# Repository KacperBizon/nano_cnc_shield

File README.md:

# Arduino Nano CNC shield

### How to use
- Install [LaserGRBL](https://github.com/arkypita/LaserGRBL/releases)
- Upload [GRBL](https://github.com/gnea/grbl) code to Arduino 

### Components
* Arduino Nano
* 2x A4988 Stepper motor drivers
* 1x IRFZ44N N-CHANNEL MOSFET
* 1x LM7805 Voltage regulator with Heatsink (note the regulator is now rotated on the PCB)
* 1x 47, 1x 1k and 1x 10k resistor
* 3mm diode
* slide switch (SS12D00)
* 1x 1000uF 16V capacitor or 2x 100uF capacitors
* 1x 2.5mm JST XH-Style 2pin male connector
* male and female header pins

### Acknowledgments
The project is based on [DIY-Mini-CNC-Laser-Engraver](https://www.instructables.com/DIY-Mini-CNC-Laser-Engraver/)

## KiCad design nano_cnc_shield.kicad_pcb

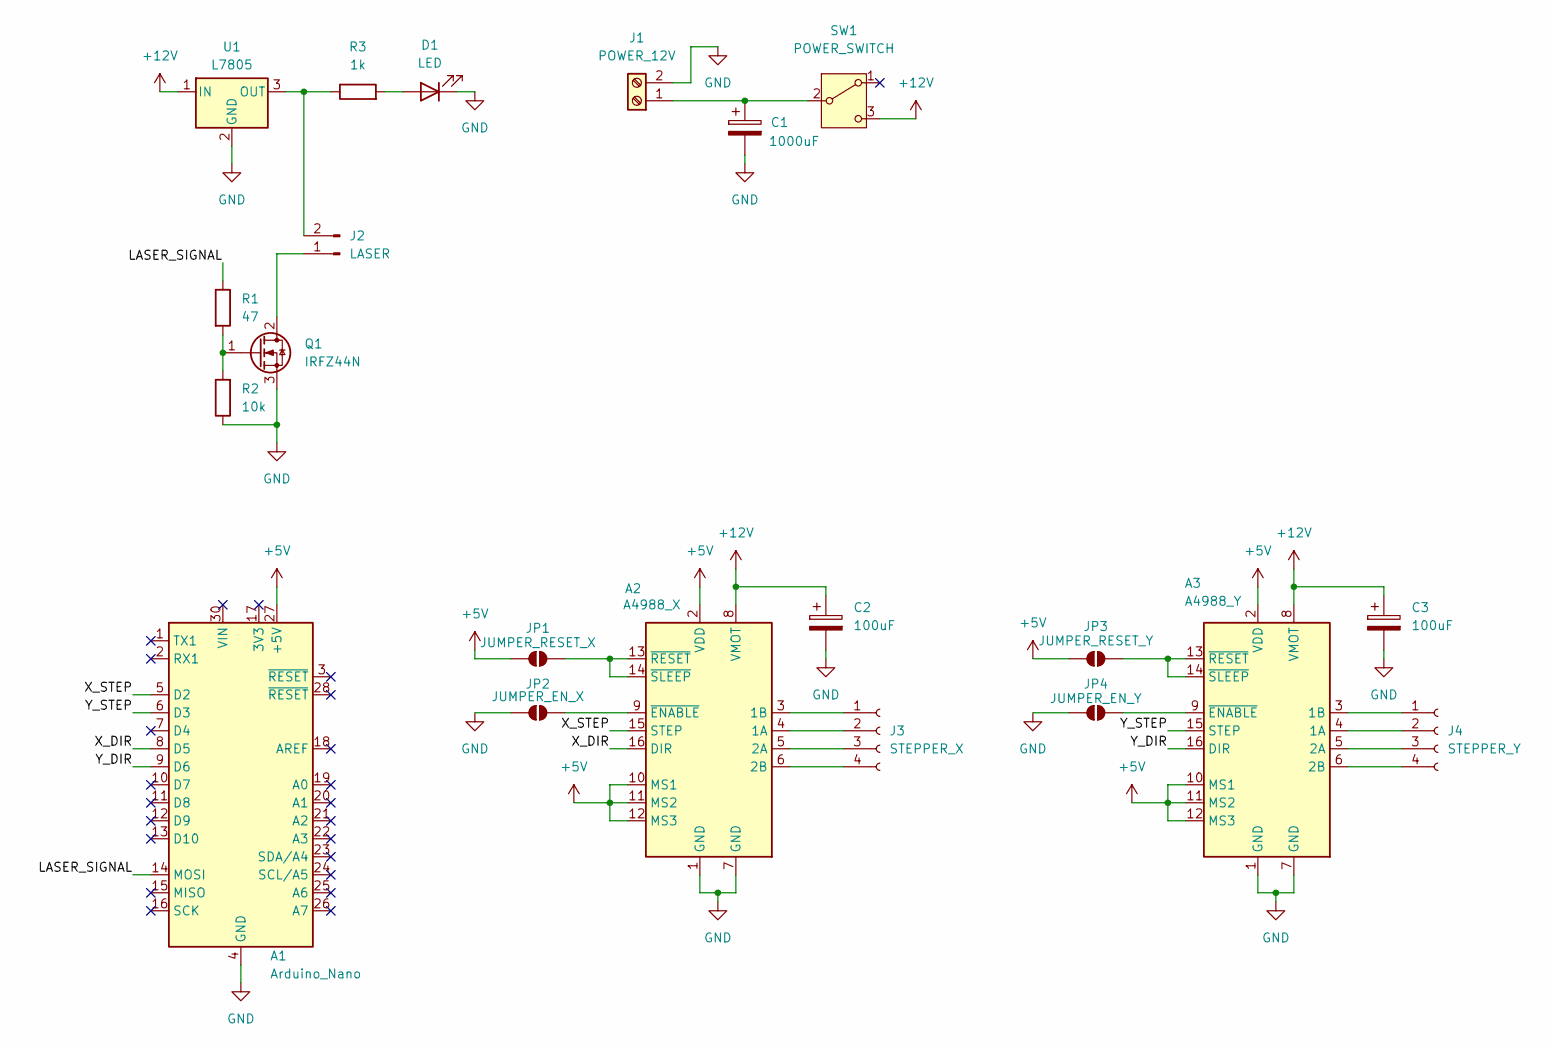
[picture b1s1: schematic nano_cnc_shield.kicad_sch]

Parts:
A1: Arduino_Nano
A2: A4988_X; Pololu_Breakout-16_15.2x20.3mm
A3: A4988_Y; Pololu_Breakout-16_15.2x20.3mm
C1: 1000uF; CP_Radial_D13.0mm_P5.00mm
C2, C3: 100uF; CP_Radial_D8.0mm_P3.50mm
D1: LED; LED_D3.0mm
J1: POWER_12V; TerminalBlock_RND_205-00045_1x02_P5.00mm_Horizontal
J2: LASER; PinSocket_1x02_P2.54mm_Vertical
J3: STEPPER_X; PinSocket_1x04_P2.54mm_Vertical
J4: STEPPER_Y; PinSocket_1x04_P2.54mm_Vertical
JP1: JUMPER_RESET_X; SolderJumper-2_P1.3mm_Open_Pad1.0x1.5mm
JP2: JUMPER_EN_X; SolderJumper-2_P1.3mm_Open_Pad1.0x1.5mm
JP3: JUMPER_RESET_Y; SolderJumper-2_P1.3mm_Open_Pad1.0x1.5mm
JP4: JUMPER_EN_Y; SolderJumper-2_P1.3mm_Open_Pad1.0x1.5mm
Q1: IRFZ44N; TO-220-3_Vertical
R1: 47; R_Axial_DIN0207_L6.3mm_D2.5mm_P10.16mm_Horizontal
R2: 10k; R_Axial_DIN0207_L6.3mm_D2.5mm_P10.16mm_Horizontal
R3: 1k; R_Axial_DIN0207_L6.3mm_D2.5mm_P10.16mm_Horizontal
SW1: POWER_SWITCH; SW_Slide-03_SS22T35_8.4x3.8x6.8_P2.54mm
U1: L7805; TO-220F-3_Vertical

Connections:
+5V: A1.27 (+5V), A2.2 (VDD), A2.10 (MS1), A2.11 (MS2), A2.12 (MS3), A3.2 (VDD), A3.10 (MS1), A3.11 (MS2), A3.12 (MS3), JP1.1 (A), JP3.1 (A)
+12V: A2.8 (VMOT), A3.8 (VMOT), C2.1, C3.1, SW1.3 (C), U1.1 (IN)
/LASER_SIGNAL: A1.14 (MOSI), R1.1
/X_DIR: A1.8 (D5), A2.16 (DIR)
/X_STEP: A1.5 (D2), A2.15 (STEP)
/Y_DIR: A1.9 (D6), A3.16 (DIR)
/Y_STEP: A1.6 (D3), A3.15 (STEP)
GND: A1.4 (GND), A1.29 (GND), A2.1 (GND), A2.7 (GND), A3.1 (GND), A3.7 (GND), C1.2, C2.2, C3.2, D1.1 (K), J1.2 (GND), JP2.1 (A), JP4.1 (A), Q1.3 (S), R2.1, U1.2 (GND)
unnamed: A2.4 (1A), J3.2
unnamed: A2.3 (1B), J3.1
unnamed: A2.5 (2A), J3.3
unnamed: A2.6 (2B), J3.4
unnamed: A2.9 (~ENABLE), JP2.2 (B)
unnamed: A2.13 (~RESET), A2.14 (~SLEEP), JP1.2 (B)
unnamed: A3.4 (1A), J4.2
unnamed: A3.3 (1B), J4.1
unnamed: A3.5 (2A), J4.3
unnamed: A3.6 (2B), J4.4
unnamed: A3.9 (~ENABLE), JP4.2 (B)
unnamed: A3.13 (~RESET), A3.14 (~SLEEP), JP3.2 (B)
unnamed: D1.2 (A), R3.2
unnamed: C1.1, J1.1 (V+), SW1.2 (B)
unnamed: J2.1, Q1.2 (D)
unnamed: J2.2, R3.1, U1.3 (OUT)
unnamed: Q1.1 (G), R1.2, R2.2

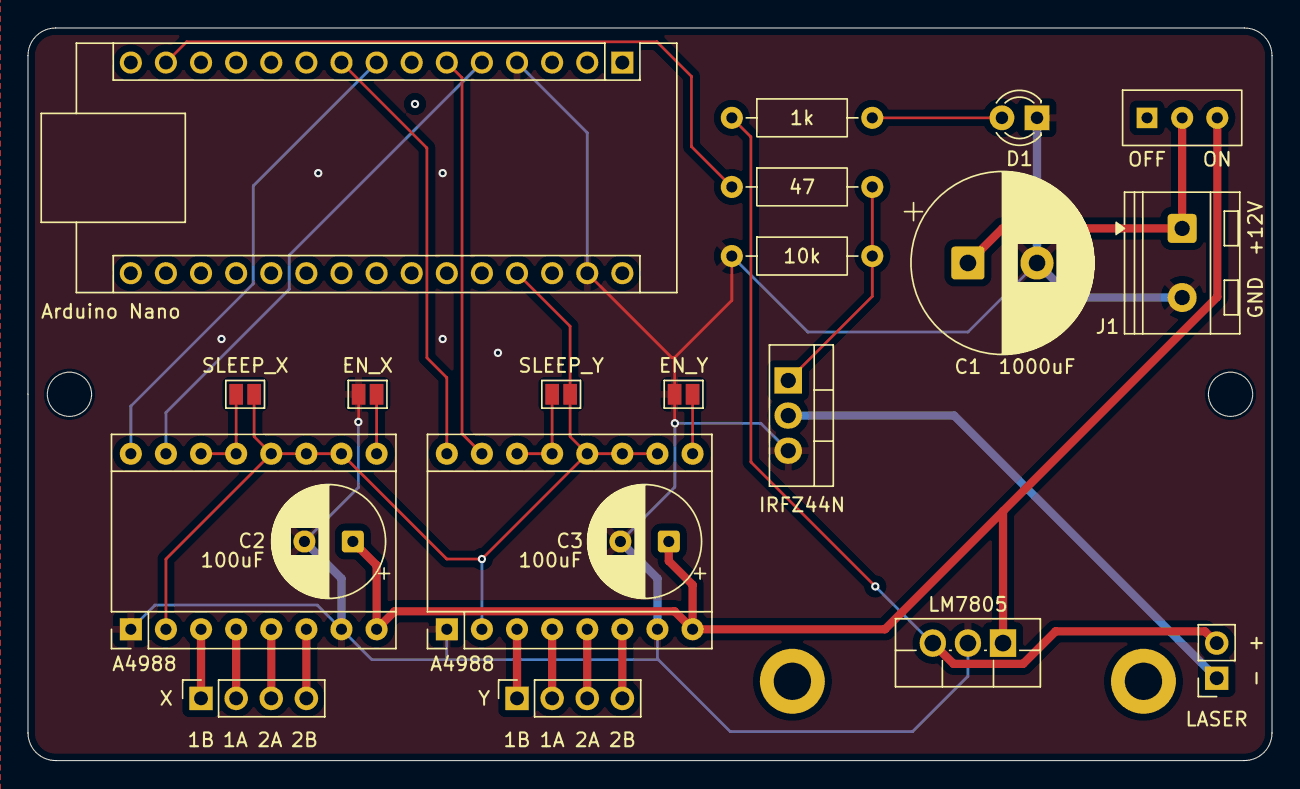
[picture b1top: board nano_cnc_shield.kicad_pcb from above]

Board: 2 copper layers, 90.0 x 53.0 mm, 25 parts (0 on the bottom side), 25 nets.

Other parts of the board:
MH1, MH2: MountingHole_3.2mm_M3_DIN965
MH3, MH4: MountingHole_2.7mm_M2.5_DIN965_Pad

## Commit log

2026-02-22 add components
2026-02-22 add complimentary components
2026-02-23 finished schematic
2026-02-23 finished layout
2026-02-24 add general routing
2026-02-24 final layout
2026-02-24 production
2026-03-10 flip LM7805, move heatsink pads
2026-03-15 add README
2026-03-15 Update README formatting
